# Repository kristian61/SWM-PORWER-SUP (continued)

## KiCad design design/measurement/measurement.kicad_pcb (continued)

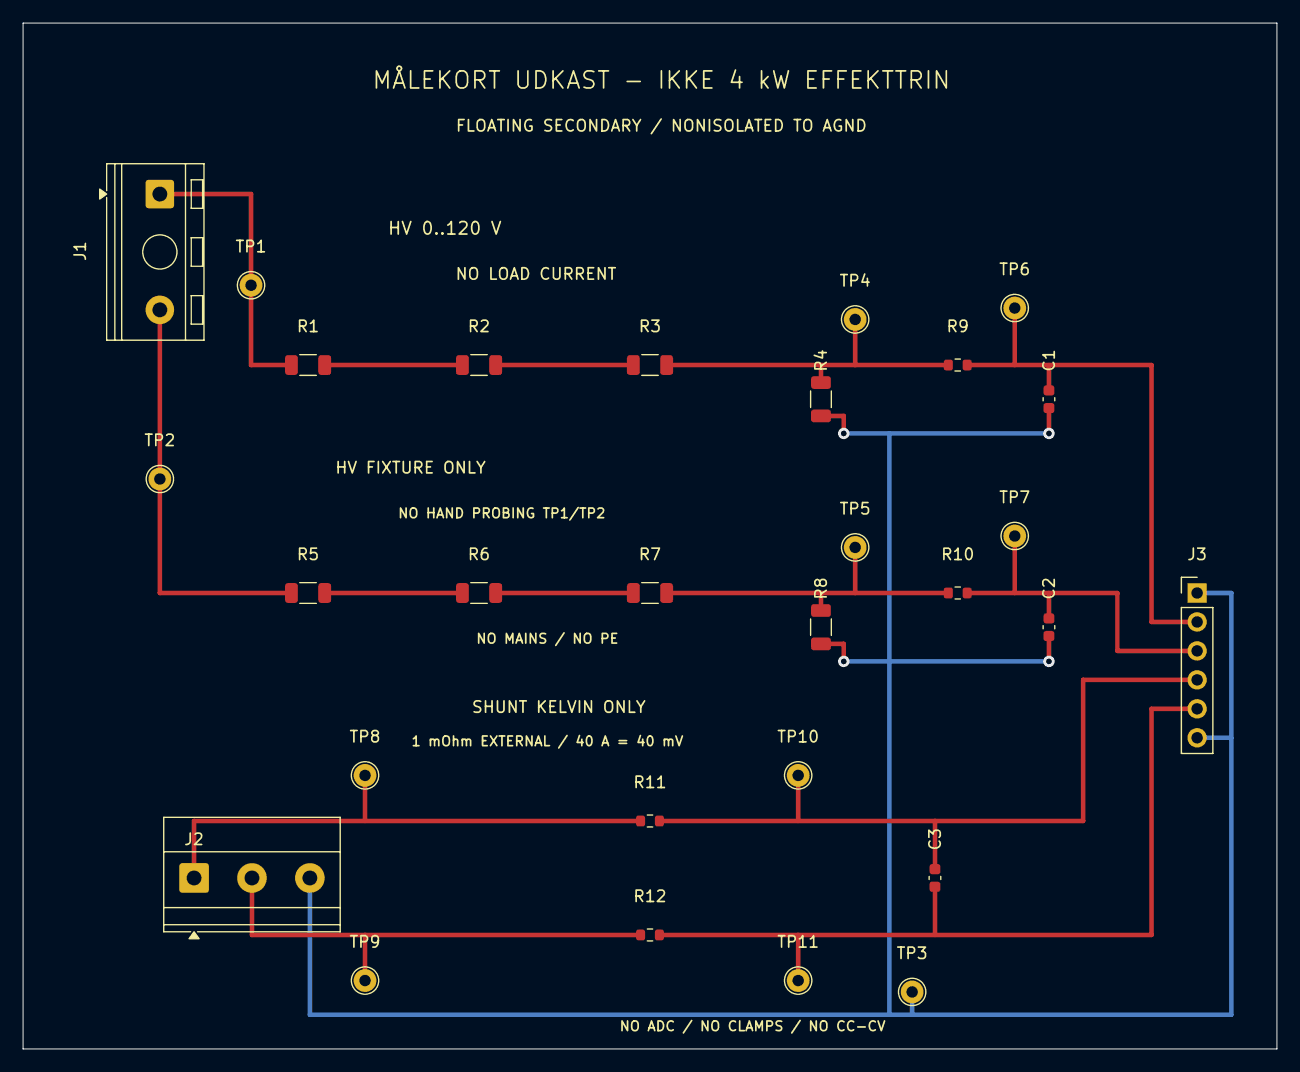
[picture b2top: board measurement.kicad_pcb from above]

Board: 2 copper layers, 110.0 x 90.0 mm, 29 parts (0 on the bottom side), 15 nets.

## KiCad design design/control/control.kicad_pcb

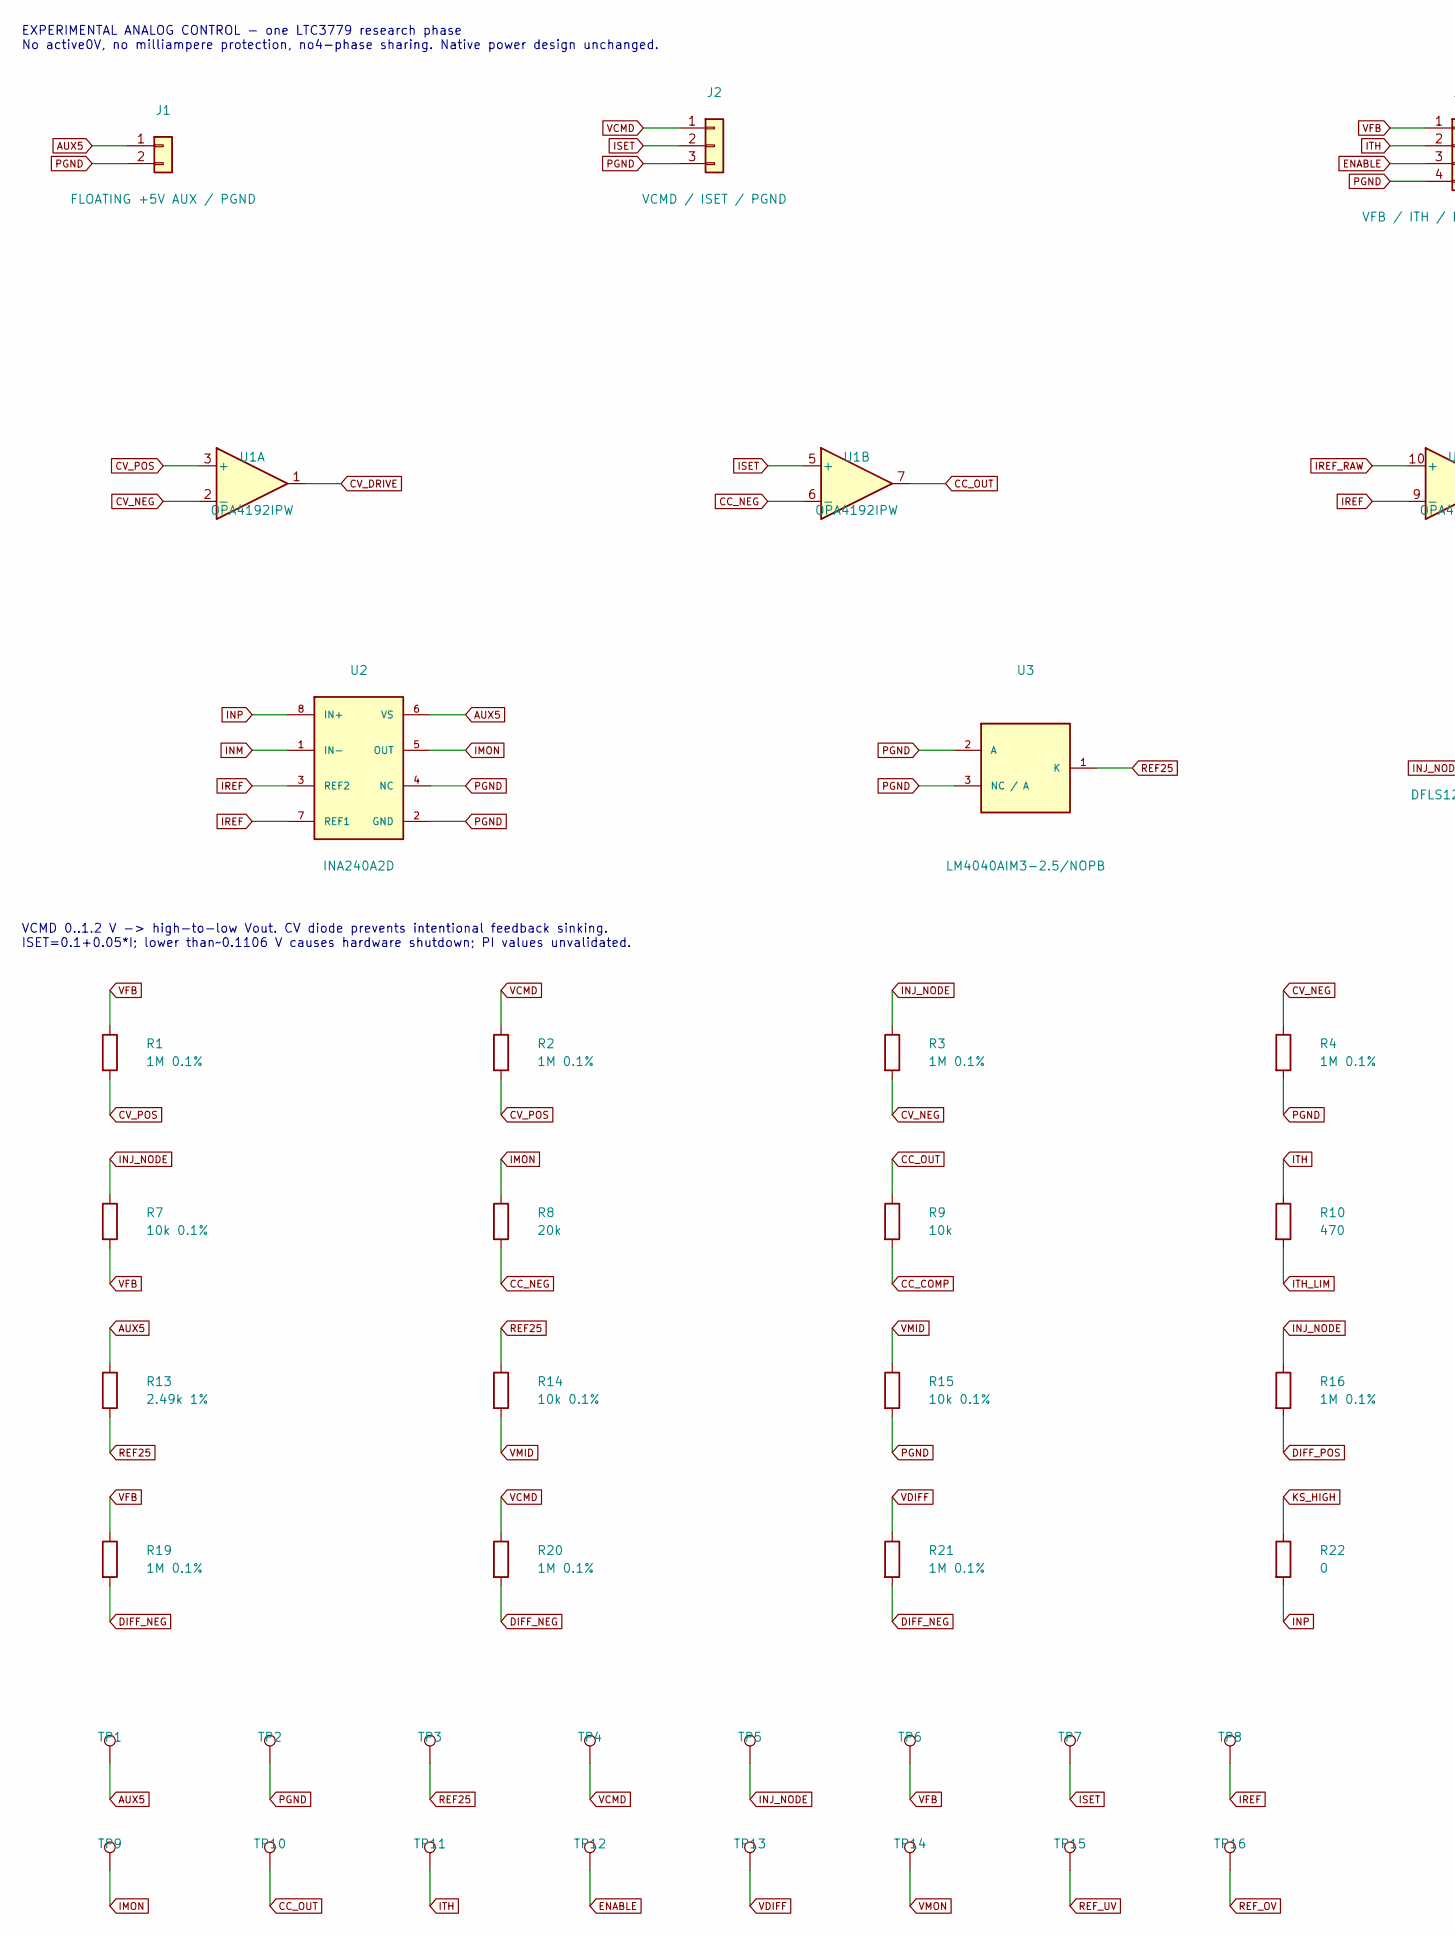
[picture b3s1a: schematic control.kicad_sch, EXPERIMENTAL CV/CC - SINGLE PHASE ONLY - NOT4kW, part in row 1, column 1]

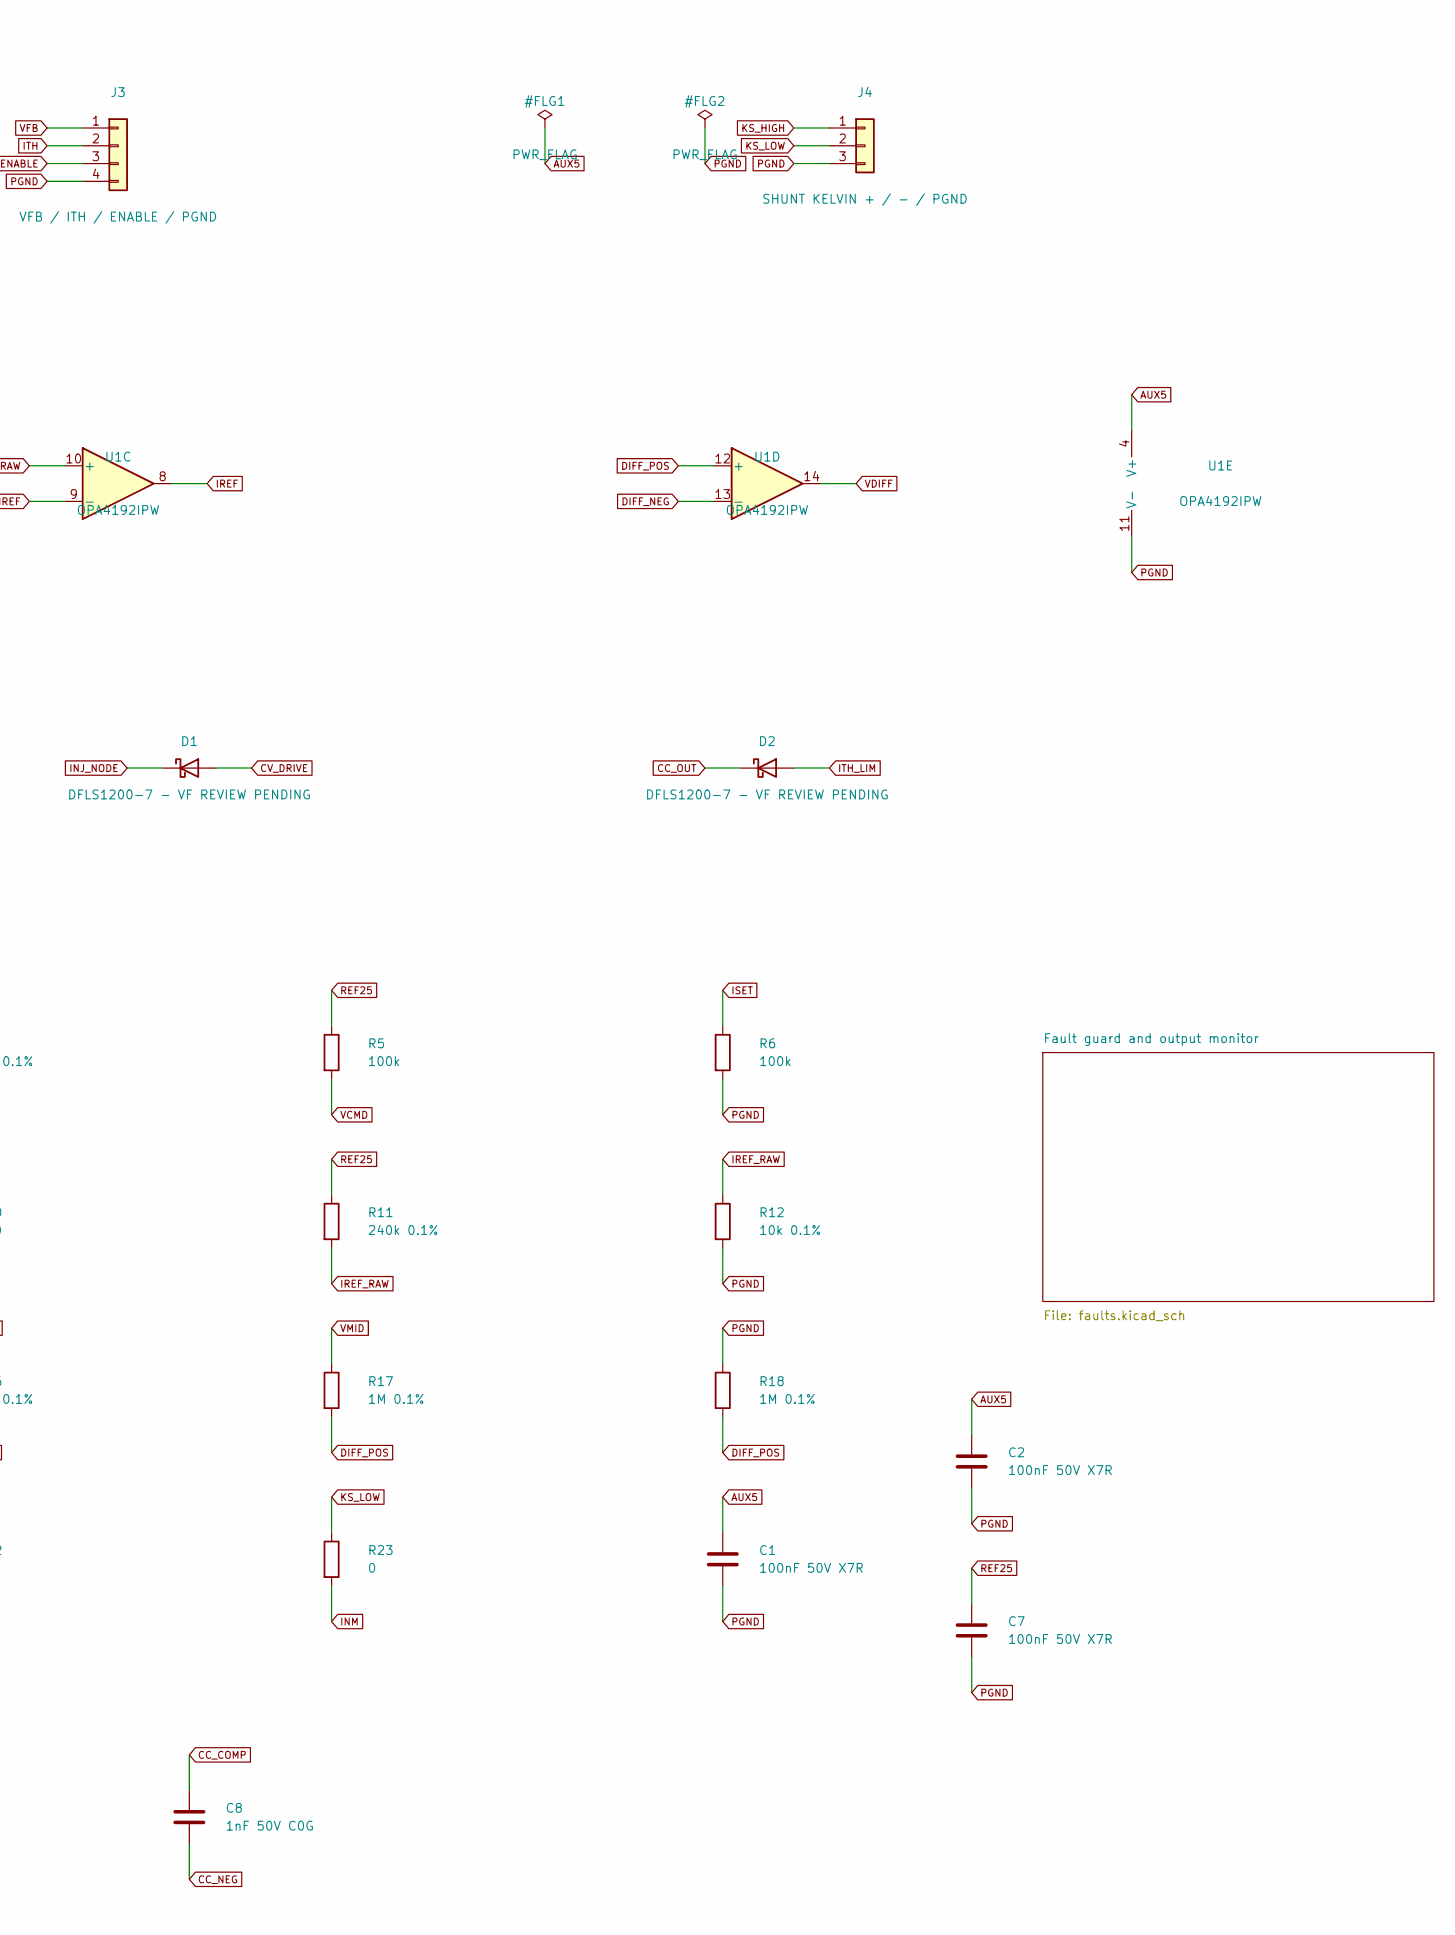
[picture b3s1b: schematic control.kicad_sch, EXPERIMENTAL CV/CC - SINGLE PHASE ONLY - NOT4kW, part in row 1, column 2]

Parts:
C1, C2, C7: 100nF 50V X7R; C_0603_1608Metric
C8: 1nF 50V C0G; C_0603_1608Metric
D1, D2: DFLS1200-7 - VF REVIEW PENDING; D_PowerDI-123
J1: FLOATING +5V AUX / PGND; PinHeader_1x02_P2.54mm_Vertical
J2: VCMD / ISET / PGND; PinHeader_1x03_P2.54mm_Vertical
J3: VFB / ITH / ENABLE / PGND; PinHeader_1x04_P2.54mm_Vertical
J4: SHUNT KELVIN + / - / PGND; PinHeader_1x03_P2.54mm_Vertical
R1, R2, R3, R4, R16, R17, R18, R19, R20, R21: 1M 0.1%; R_0603_1608Metric
R5, R6: 100k; R_0603_1608Metric
R7, R12, R14, R15: 10k 0.1%; R_0603_1608Metric
R8: 20k; R_0603_1608Metric
R9: 10k; R_0603_1608Metric
R10: 470; R_0603_1608Metric
R11: 240k 0.1%; R_0603_1608Metric
R13: 2.49k 1%; R_0603_1608Metric
R22, R23: 0; R_0603_1608Metric
TP1: AUX5; TestPoint_THTPad_D2.0mm_Drill1.0mm
TP2: PGND; TestPoint_THTPad_D2.0mm_Drill1.0mm
TP3: REF25; TestPoint_THTPad_D2.0mm_Drill1.0mm
TP4: VCMD; TestPoint_THTPad_D2.0mm_Drill1.0mm
TP5: INJ_NODE; TestPoint_THTPad_D2.0mm_Drill1.0mm
TP6: VFB; TestPoint_THTPad_D2.0mm_Drill1.0mm
TP7: ISET; TestPoint_THTPad_D2.0mm_Drill1.0mm
TP8: IREF; TestPoint_THTPad_D2.0mm_Drill1.0mm
TP9: IMON; TestPoint_THTPad_D2.0mm_Drill1.0mm
TP10: CC_OUT; TestPoint_THTPad_D2.0mm_Drill1.0mm
TP11: ITH; TestPoint_THTPad_D2.0mm_Drill1.0mm
TP12: ENABLE; TestPoint_THTPad_D2.0mm_Drill1.0mm
TP13: VDIFF; TestPoint_THTPad_D2.0mm_Drill1.0mm
TP14: VMON; TestPoint_THTPad_D2.0mm_Drill1.0mm
TP15: REF_UV; TestPoint_THTPad_D2.0mm_Drill1.0mm
TP16: REF_OV; TestPoint_THTPad_D2.0mm_Drill1.0mm
U1: OPA4192IPW; TSSOP-14_4.4x5mm_P0.65mm
U2: INA240A2D; SOIC-8_3.9x4.9mm_P1.27mm
U3: LM4040AIM3-2.5/NOPB; SOT-23

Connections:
AUX5: C1.1, C2.1, J1.1, R13.1, TP1.1, U1.4 (V+), U2.6 (VS); also elsewhere on the board
CC_COMP: C8.1, R9.2
CC_NEG: C8.2, R8.2, U1.6 (-)
CC_OUT: D2.1 (K), R9.1, TP10.1, U1.7
CV_DRIVE: D1.2 (A), U1.1
CV_NEG: R3.2, R4.1, U1.2 (-)
CV_POS: R1.2, R2.2, U1.3 (+)
DIFF_NEG: R19.2, R20.2, R21.2, U1.13 (-)
DIFF_POS: R16.2, R17.2, R18.2, U1.12 (+)
ENABLE: J3.3, TP12.1; also elsewhere on the board
IMON: R8.1, TP9.1, U2.5 (OUT); also elsewhere on the board
INJ_NODE: D1.1 (K), R3.1, R7.1, R16.1, TP5.1; also elsewhere on the board
INM: R23.2, U2.1 (IN-)
INP: R22.2, U2.8 (IN+)
IREF: TP8.1, U1.8, U1.9 (-), U2.3 (REF2), U2.7 (REF1)
IREF_RAW: R11.2, R12.1, U1.10 (+)
ISET: J2.2, R6.1, TP7.1, U1.5 (+); also elsewhere on the board
ITH: J3.2, R10.1, TP11.1
ITH_LIM: D2.2 (A), R10.2
KS_HIGH: J4.1, R22.1
KS_LOW: J4.2, R23.1
PGND: C1.2, C2.2, C7.2, J1.2, J2.3, J3.4, J4.3, R4.2, R6.2, R12.2, R15.2, R18.1, TP2.1, U1.11 (V-), U2.2 (GND), U2.4 (NC), U3.2 (A), U3.3 (NC / A); also elsewhere on the board
REF25: C7.1, R5.1, R11.1, R13.2, R14.1, TP3.1, U3.1 (K); also elsewhere on the board
REF_OV: TP16.1; also elsewhere on the board
REF_UV: TP15.1; also elsewhere on the board
VCMD: J2.1, R2.1, R5.2, R20.1, TP4.1; also elsewhere on the board
VDIFF: R21.1, TP13.1, U1.14; also elsewhere on the board
VFB: J3.1, R1.1, R7.2, R19.1, TP6.1
VMID: R14.2, R15.1, R17.1
VMON: TP14.1; also elsewhere on the board

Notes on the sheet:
EXPERIMENTAL ANALOG CONTROL - one LTC3779 research phase No active0V, no milliampere protection, no4-phase sharing. Native power design unchanged.
VCMD 0..1.2 V -> high-to-low Vout. CV diode prevents intentional feedback sinking. ISET=0.1+0.05*I; lower than~0.1106 V causes hardware shutdown; PI values unvalidated.

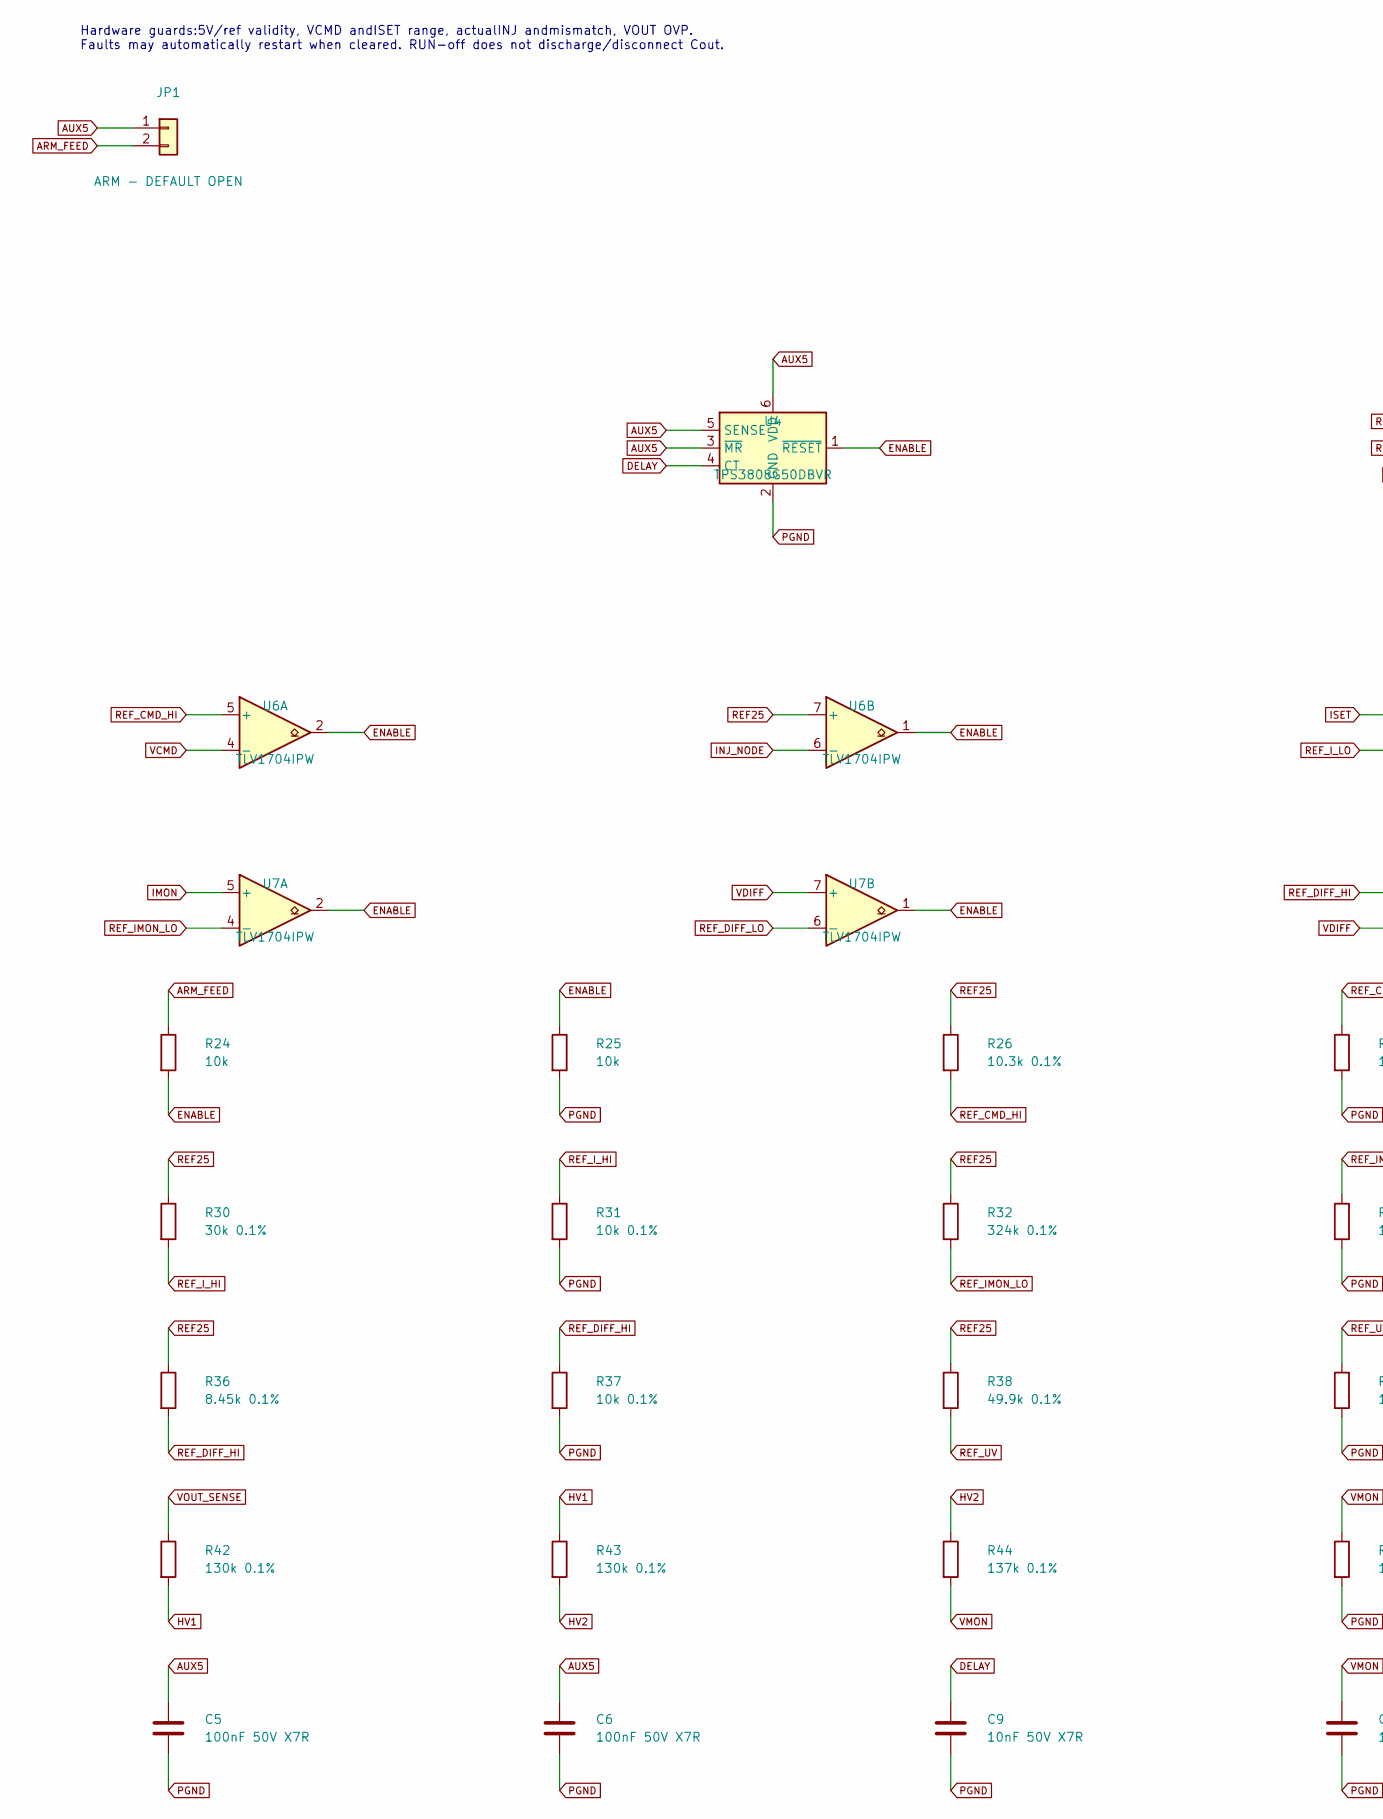
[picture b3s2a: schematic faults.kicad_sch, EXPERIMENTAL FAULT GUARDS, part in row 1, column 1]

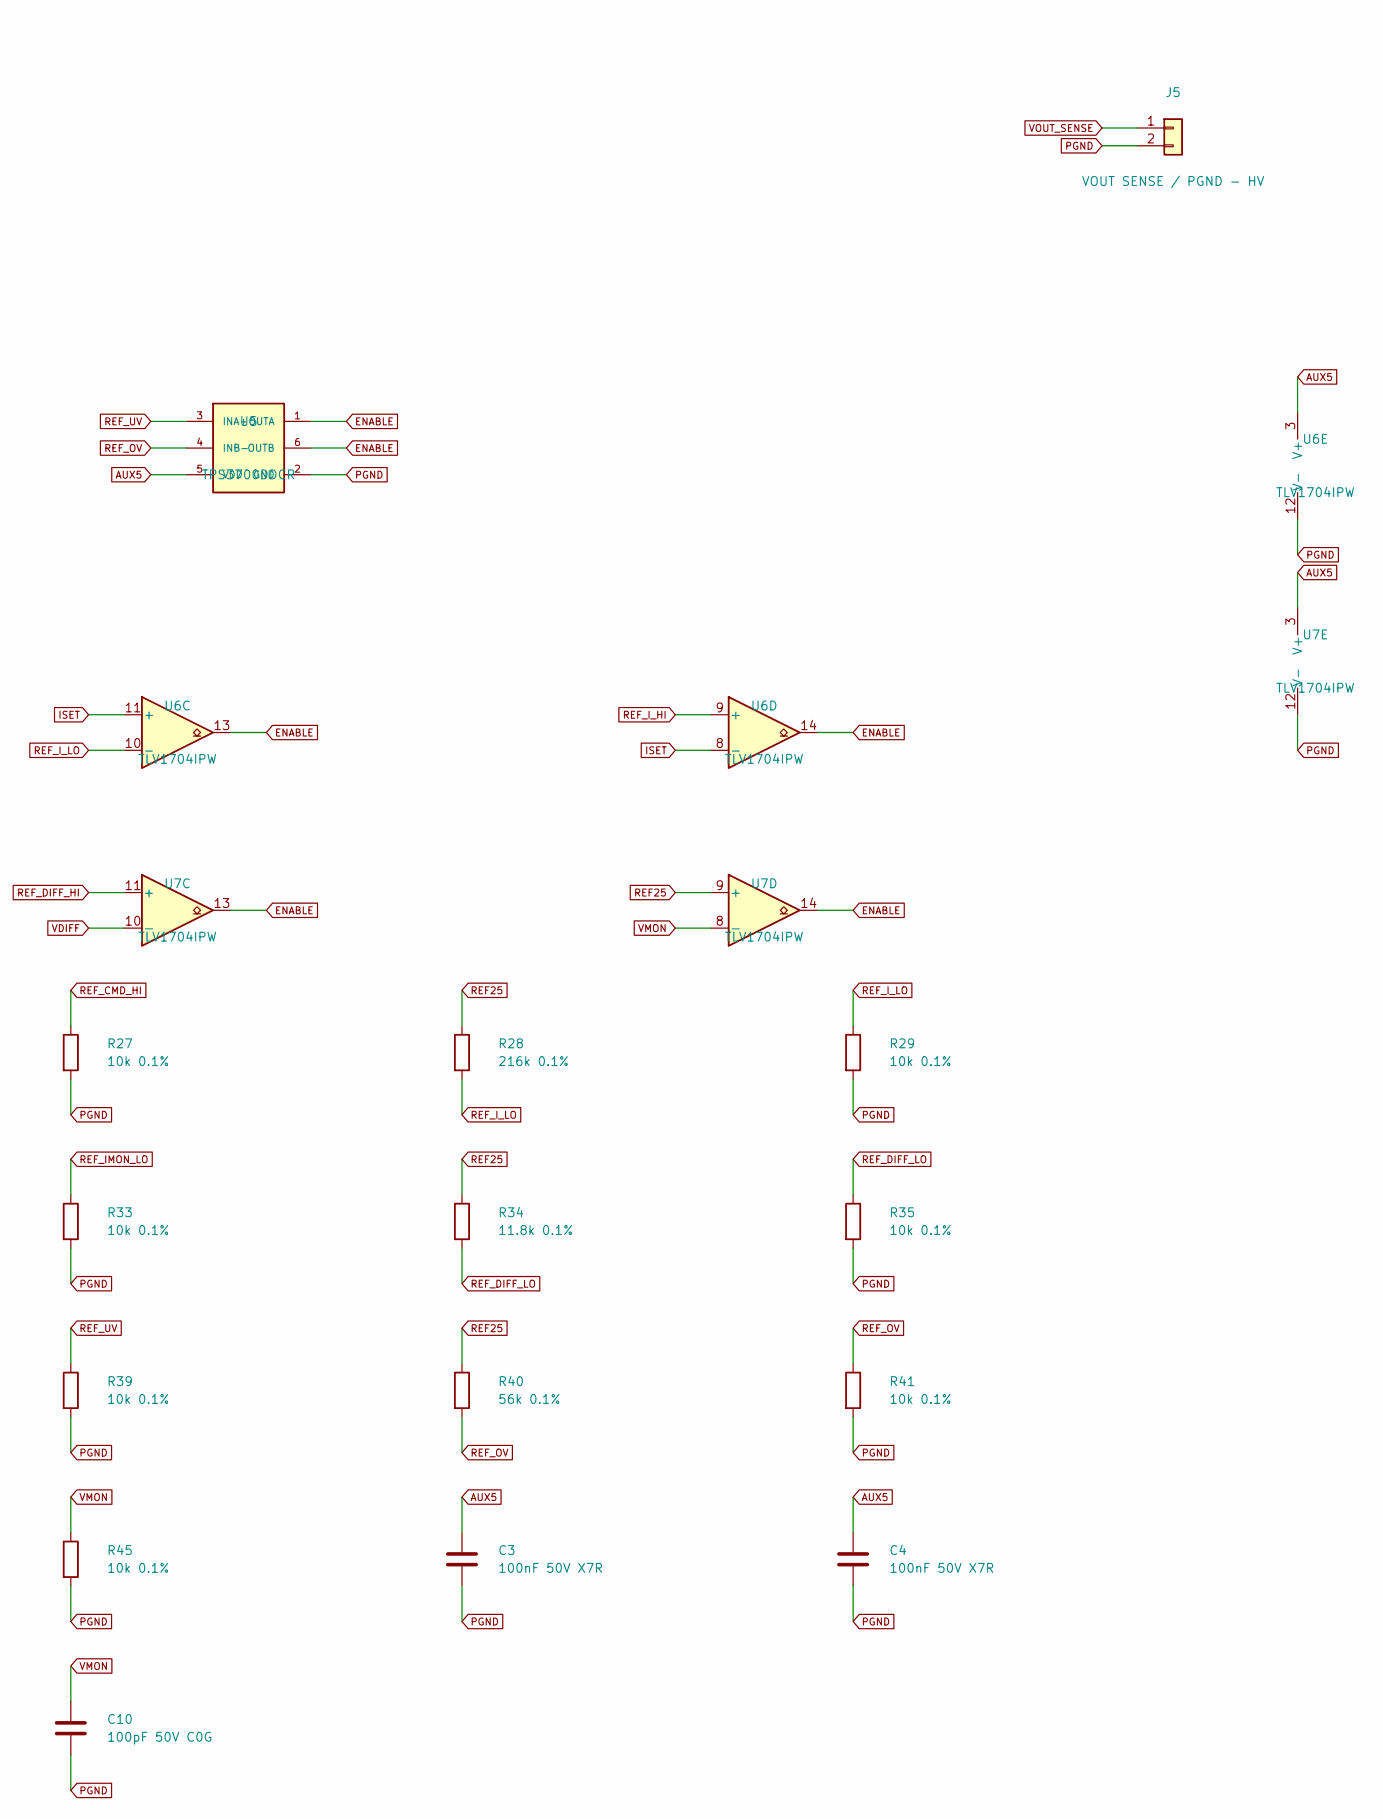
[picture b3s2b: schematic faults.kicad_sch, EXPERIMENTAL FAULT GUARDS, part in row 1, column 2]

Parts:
C3, C4, C5, C6: 100nF 50V X7R; C_0603_1608Metric
C9: 10nF 50V X7R; C_0603_1608Metric
C10: 100pF 50V C0G; C_0603_1608Metric
J5: VOUT SENSE / PGND - HV; TerminalBlock_RND_205-00241_1x02_P10.16mm_Horizontal
JP1: ARM - DEFAULT OPEN; PinHeader_1x02_P2.54mm_Vertical
R24, R25: 10k; R_0603_1608Metric
R26: 10.3k 0.1%; R_0603_1608Metric
R27, R29, R31, R33, R35, R37, R39, R41, R45: 10k 0.1%; R_0603_1608Metric
R28: 216k 0.1%; R_0603_1608Metric
R30: 30k 0.1%; R_0603_1608Metric
R32: 324k 0.1%; R_0603_1608Metric
R34: 11.8k 0.1%; R_0603_1608Metric
R36: 8.45k 0.1%; R_0603_1608Metric
R38: 49.9k 0.1%; R_0603_1608Metric
R40: 56k 0.1%; R_0603_1608Metric
R42, R43: 130k 0.1%; R_1206_3216Metric
R44: 137k 0.1%; R_1206_3216Metric
U4: TPS3808G50DBVR; SOT-23-6
U5: TPS3700DDCR; SOT-23-6
U6, U7: TLV1704IPW; TSSOP-14_4.4x5mm_P0.65mm

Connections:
ARM_FEED: JP1.2, R24.1
AUX5: C3.1, C4.1, C5.1, C6.1, JP1.1, U4.3 (~MR), U4.5 (SENSE), U4.6 (VDD), U5.5 (VDD), U6.3 (V+), U7.3 (V+); also elsewhere on the board
DELAY: C9.1, U4.4 (CT)
ENABLE: R24.2, R25.1, U4.1 (~RESET), U5.1 (OUTA), U5.6 (OUTB), U6.1, U6.2, U6.13, U6.14, U7.1, U7.2, U7.13, U7.14; also elsewhere on the board
HV1: R42.2, R43.1
HV2: R43.2, R44.1
IMON: U7.5 (+); also elsewhere on the board
INJ_NODE: U6.6 (-); also elsewhere on the board
ISET: U6.8 (-), U6.11 (+); also elsewhere on the board
PGND: C3.2, C4.2, C5.2, C6.2, C9.2, C10.2, J5.2, R25.2, R27.2, R29.2, R31.2, R33.2, R35.2, R37.2, R39.2, R41.2, R45.2, U4.2 (GND), U5.2 (GND), U6.12 (V-), U7.12 (V-); also elsewhere on the board
REF25: R26.1, R28.1, R30.1, R32.1, R34.1, R36.1, R38.1, R40.1, U6.7 (+), U7.9 (+); also elsewhere on the board
REF_CMD_HI: R26.2, R27.1, U6.5 (+)
REF_DIFF_HI: R36.2, R37.1, U7.11 (+)
REF_DIFF_LO: R34.2, R35.1, U7.6 (-)
REF_IMON_LO: R32.2, R33.1, U7.4 (-)
REF_I_HI: R30.2, R31.1, U6.9 (+)
REF_I_LO: R28.2, R29.1, U6.10 (-)
REF_OV: R40.2, R41.1, U5.4 (INB-); also elsewhere on the board
REF_UV: R38.2, R39.1, U5.3 (INA+); also elsewhere on the board
VCMD: U6.4 (-); also elsewhere on the board
VDIFF: U7.7 (+), U7.10 (-); also elsewhere on the board
VMON: C10.1, R44.2, R45.1, U7.8 (-); also elsewhere on the board
VOUT_SENSE: J5.1, R42.1

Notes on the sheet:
Hardware guards:5V/ref validity, VCMD andISET range, actualINJ andmismatch, VOUT OVP. Faults may automatically restart when cleared. RUN-off does not discharge/disconnect Cout.

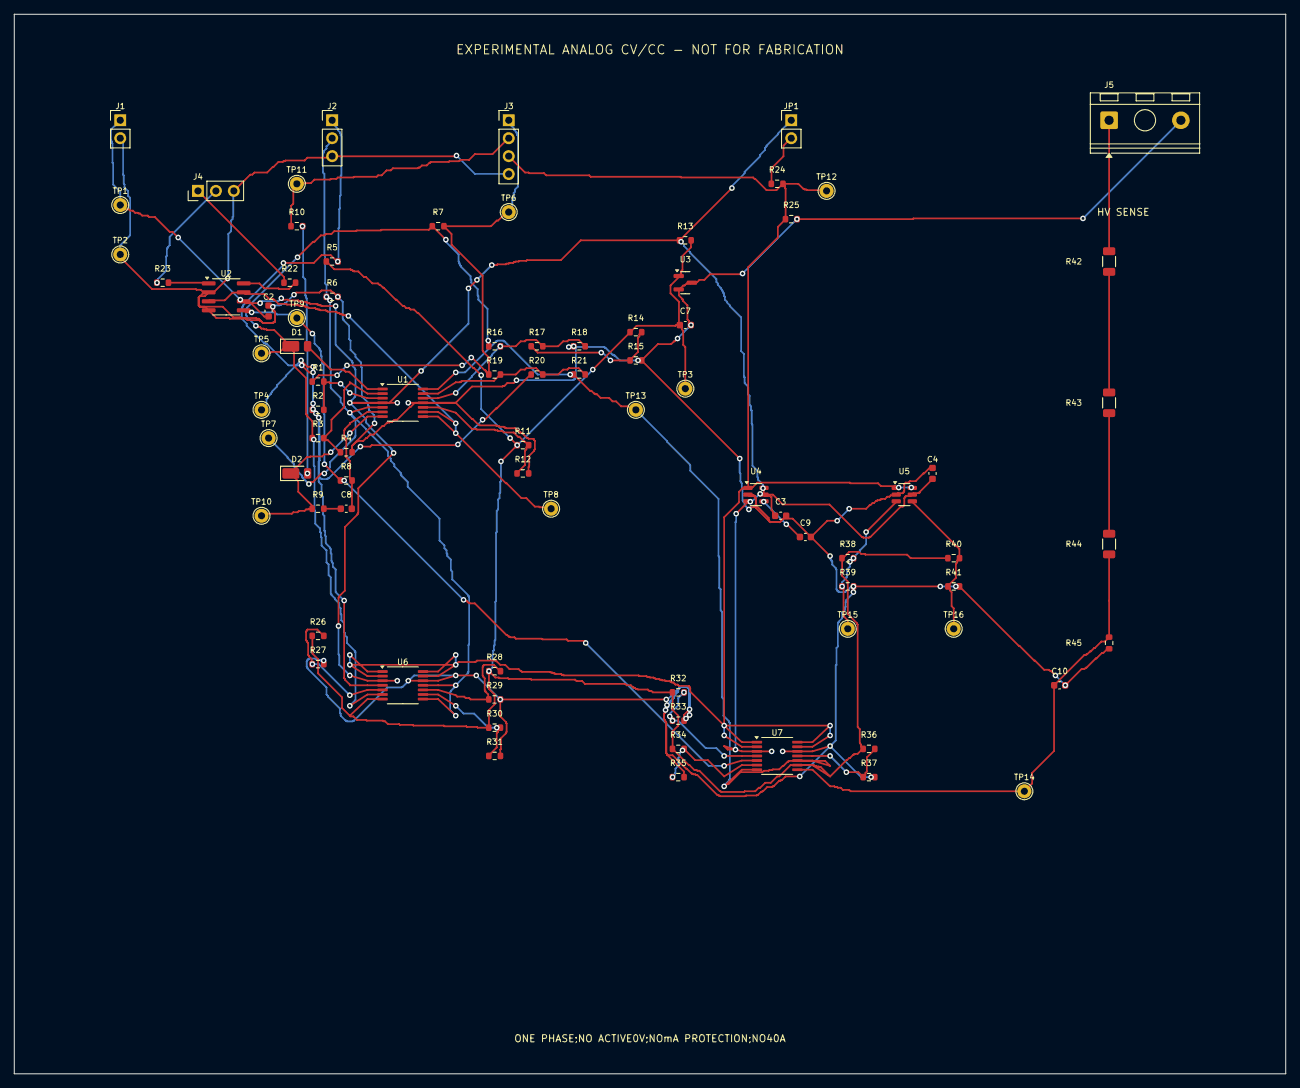
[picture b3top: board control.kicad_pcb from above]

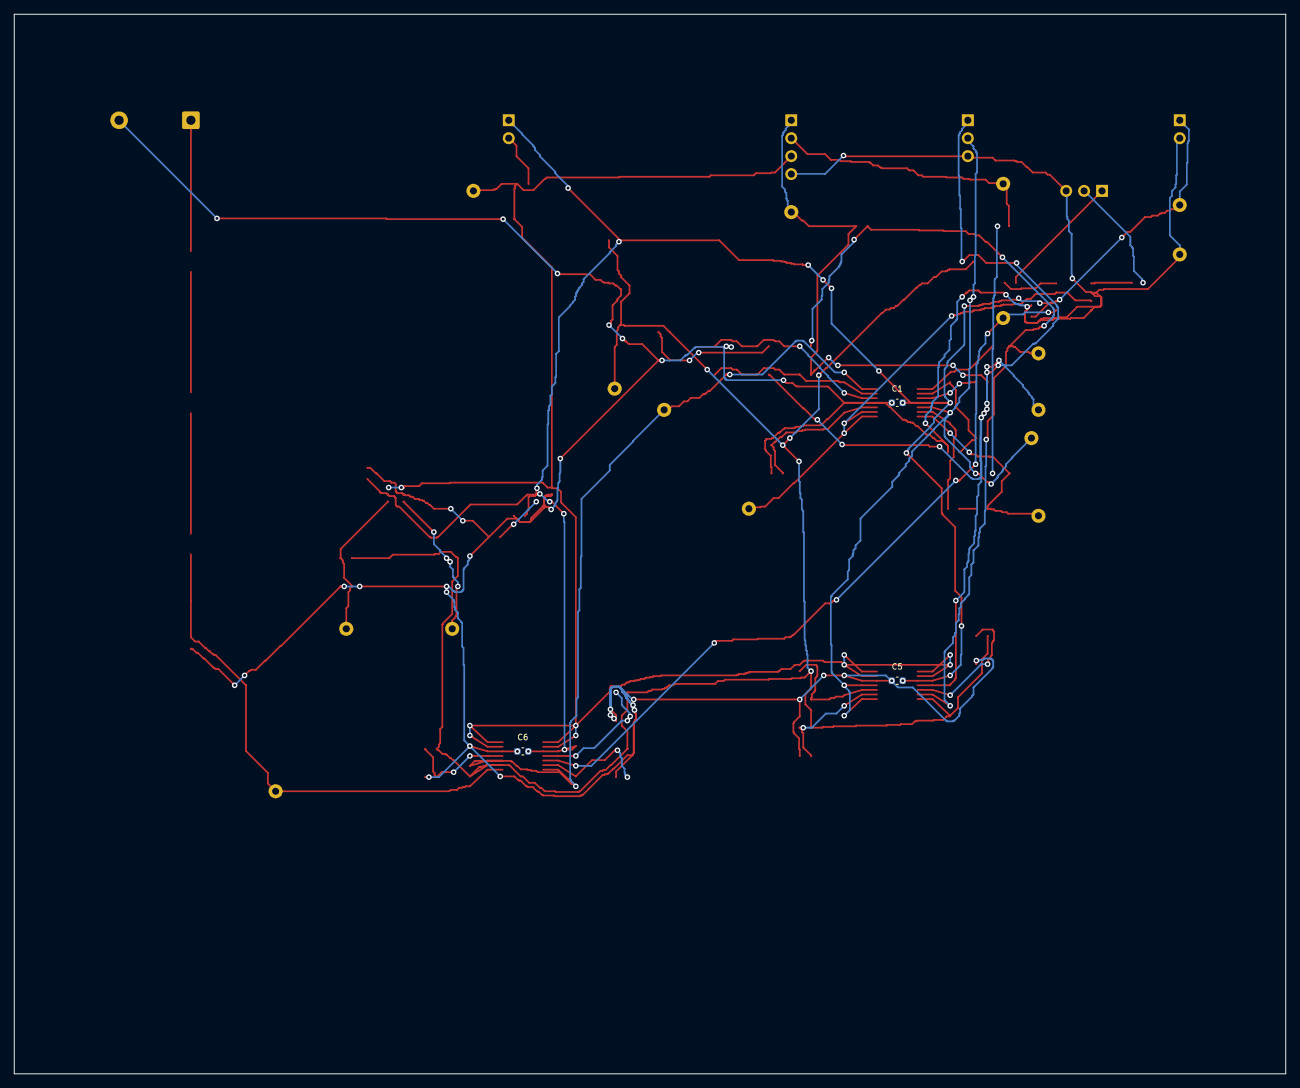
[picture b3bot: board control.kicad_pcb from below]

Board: 2 copper layers, 180.0 x 150.0 mm, 86 parts (3 on the bottom side), 41 nets.

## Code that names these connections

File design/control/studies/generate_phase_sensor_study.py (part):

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for unit,nets,xy,desc in ampunits:add('U2','OPA4192PW',LIB+':OPA4192',nets,xy,desc,'Package_SO:TSSOP-14_4.4x5mm_P0.65mm',TI+'opa192.pdf',unit=unit,status='MANUFACTURER FAMILY PINOUT VERIFIED; PI DYNAMICS UNVALIDATED')
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add('J1','PHASE OUTPUT / COMMON OUTPUT','Connector_Generic:Conn_01x02',{'1':'PHASE_OUT','2':'VOUT_COMMON'},(45.72,129.54),'Externalpower/shuntinterface:>=25A>=200VterminalMPNpending.',board=False)
add('J2','AUX5 / PGND / REF1V25 / ICMD','Connector_Generic:Conn_01x04',{'1':'AUX5','2':'PGND','3':'VREF_IN','4':'ICMD'},(144.78,116.84),'Qualifiedfloating-secondarysupply/reference/perphasecommand.NotPE.','Connector_PinHeader_2.54mm:PinHeader_1x04_P2.54mm_Vertical')
add('J3','ITH / RUN / DIAG / PGND','Connector_Generic:Conn_01x04',{'1':'ITH_LOCAL','2':'RUN_LOCAL','3':'DIAG','4':'PGND'},(180.34,116.84),'ExternalguardedRUNdriver/latchedshutdownnotdrawn.NeverjoinITHbetweenphases.','Connector_PinHeader_2.54mm:PinHeader_1x04_P2.54mm_Vertical')
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for idx,net in enumerate(['AUX5','PGND','HGND'],1):add('#FLG'+str(idx),'PWR_FLAG','power:PWR_FLAG',{'1':net},(355.6+12.7*(idx-1),27.94),'Externallyvalidpower/referenceflag.',board=False)
# Give the delivered BOM readable Danish functions; source/provenance fields stay exact.
descriptions={
 'U1':'Isoleret phasesensor med intern DC/DC. HGND følger den fælles positive udgang; PGND er den flydende sekundærretur. Originalt TI-pinout verificeret.',
 'U2':'OPA4192: A konverterer OUTP-OUTN til 1,25 V offset; B regulerer lokal strøm via PI og NMOS; C buffer referencen; D er ubrugt follower. PI-stabilitet er uverificeret.',
 'SH1':'Ekstern 2 mΩ fireterminal-shunt pr. fase, 0,1 %, mindst 3 W, mindst 25 A, højst 15 ppm/°C og mindst 200 V arbejdsrating som krav. MPN og Kelvin-montage mangler.',
 'Q1':'Lokal 12 V N-MOSFET-kandidat til ITH-sink. Gate tåler højst 8 V. Fysisk G1/S2/D3-mapping er afledt af TI-views og kræver uafhængigt review; landpattern mangler.',
 'J1':'Power-/shuntgrænseflade til én fases outputgren og fælles VOUT. Endeligt stik eller busbar med mindst 25 A og 200 V rating mangler.',
 'J2':'Eksternt kvalificeret AUX5, PGND, 1,25 V reference og individuel strømkommando. PGND tilhører flydende sekundærside.',
 'J3':'Kun denne fases ITH, RUN, DIAG og PGND. RUN-guard og fejllåsning er ikke tegnet; ITH må aldrig deles med andre faser.',
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net_components={c.get('ref'):(c.findtext('value') or '',c.findtext('footprint') or '') for c in tree.findall('./components/comp') if not c.get('ref').startswith('#')}
listed_components={r['Reference']:(r['Value'],r['Footprint']) for r in rows}
assert net_components==listed_components,{'XML_only':list(set(net_components)-set(listed_components)),'BOM_only':list(set(listed_components)-set(net_components)),'mismatches':[(r,v,listed_components.get(r)) for r,v in net_components.items() if listed_components.get(r)!=v]}
sensor_datasheet_pinmap={'1':'DCDC_OUT','2':'DCDC_HGND','3':'HLDO_IN','4':'NC','5':'HLDO_OUT','6':'INP','7':'INN','8':'HGND','9':'GND','10':'OUTN','11':'OUTP','12':'VDD','13':'LDO_OUT','14':'DIAG','15':'DCDC_GND','16':'DCDC_IN'}
assert {p['number']:p['name'] for p in h.pins(LIB+':AMC3302DWE')}==sensor_datasheet_pinmap
erc_data=json.loads((D/'erc.json').read_text())
violations=[v for sheet in erc_data['sheets'] for v in sheet.get('violations',[])]
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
